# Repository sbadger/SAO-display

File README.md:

# SAO-display
Display board for SAO

My goals for this project
* create an A4 size display board with a 4x5 grid of SAO connectors
* I2c connectors should be connected so the SAO's can talk
* I2c connectoer near incoming power connector to tap into the bus
* I2c bus and clock should be easily connected or disconnected through hsolder brige or header
* expose the GPIO pins to an unpopulated header to enable if needed
* mounting holes in corners
* LED power light
* 3.3V reguator for each row

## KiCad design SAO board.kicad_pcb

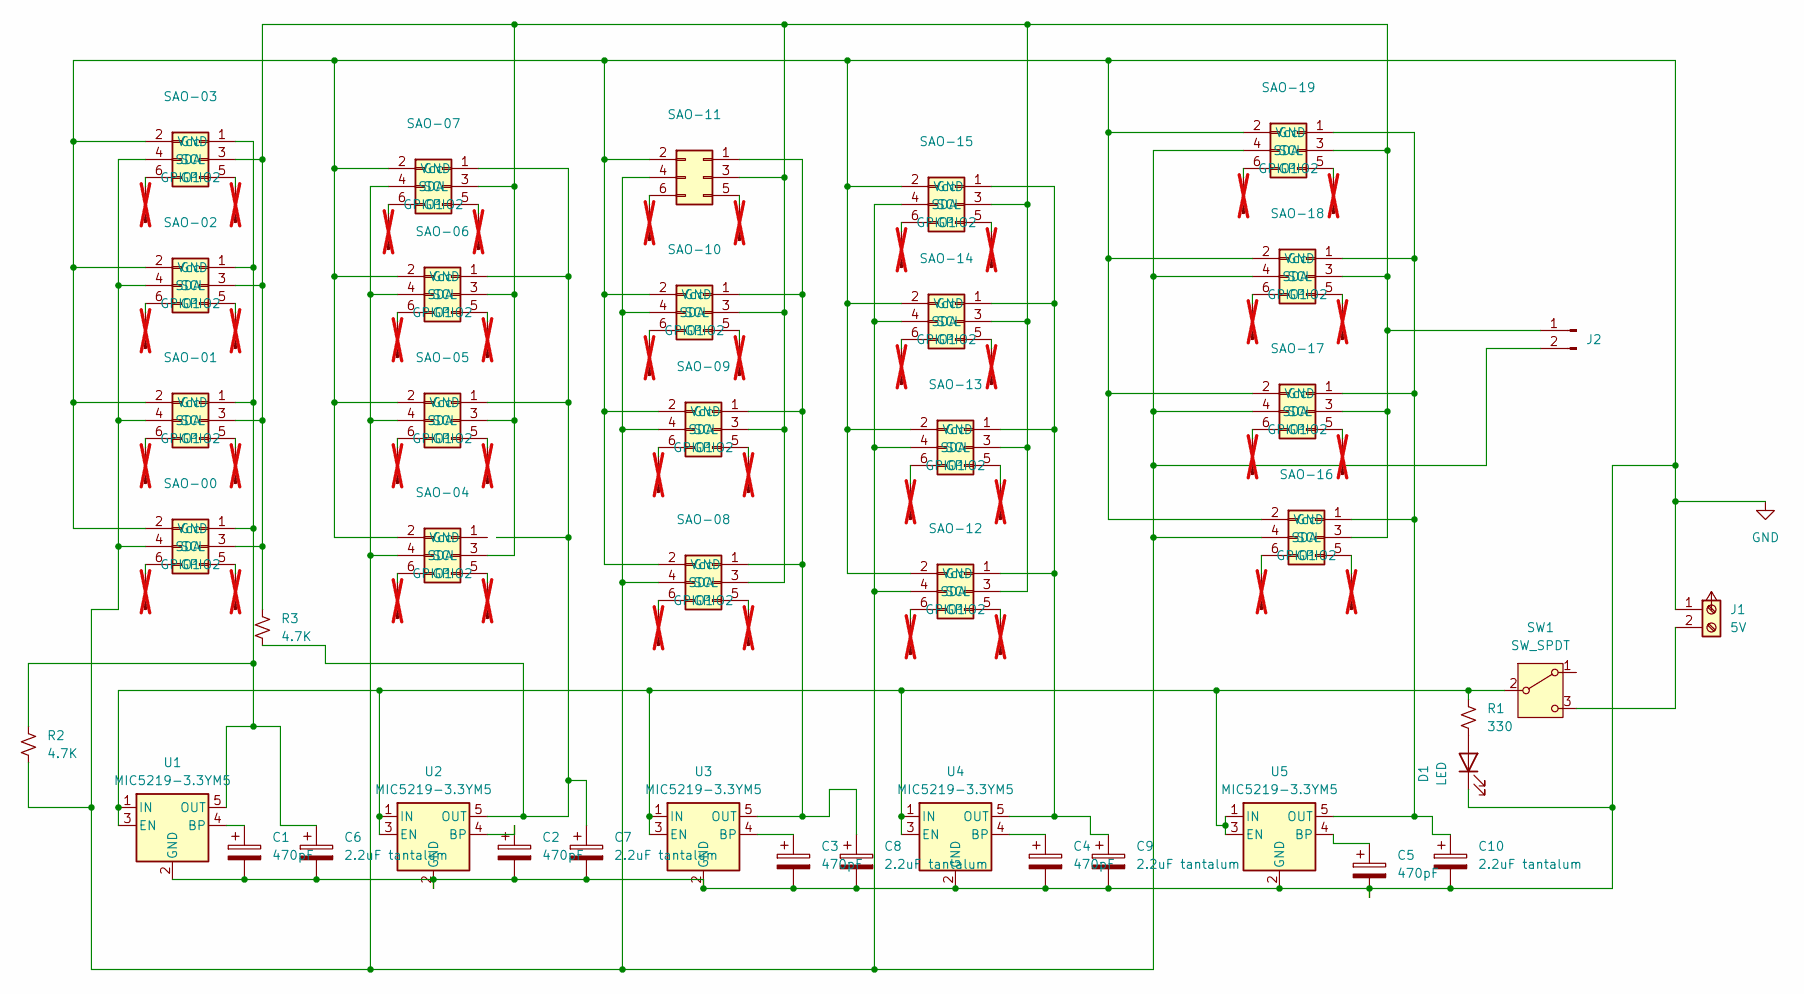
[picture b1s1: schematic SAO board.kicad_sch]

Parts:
C1, C2, C3, C4, C5: 470pF; L_1008_2520Metric
C6, C7, C8, C9, C10: 2.2uF tantalum; L_1008_2520Metric
D1: LED; L_1008_2520Metric
J1: 5V; TerminalBlock_Phoenix_PT-1,5-2-5.0-H_1x02_P5.00mm_Horizontal
J2: PinHeader_1x02_P2.54mm_Vertical
J3, J4, J5, J6, J7, J8, J9, J10, J11, J12, J13, J14, J15, J16, J17, J18, J19, J20, J21, J22, J23, J24, J25, J26, J27, J28, J29, J30, J31, J32, J33, J34, J35, J36, J37, J38, J39, J40, J41, J42: Conn_01x01_Pin; PinHeader_1x01_P2.54mm_Horizontal; not fitted
R1: 330; L_1008_2520Metric
R2, R3: 4.7K; L_1008_2520Metric
SAO-00, SAO-01, SAO-02, SAO-03, SAO-04, SAO-05, SAO-06, SAO-07, SAO-08, SAO-09, SAO-10, SAO-11, SAO-12, SAO-13, SAO-14, SAO-15, SAO-16, SAO-17, SAO-18, SAO-19: SAO; PinHeader_2x03_P2.54mm_Vertical
SW1: SW_SPDT; SW_Slide-03_Wuerth-WS-SLTV_10x2.5x6.4_P2.54mm
U1, U2, U3, U4, U5: MIC5219-3.3YM5; SOT-23-5

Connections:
GND: C1.2, C2.2, C3.2, C4.2, C5.2, C6.2, C7.2, C8.2, C9.2, C10.2, D1.1 (K), J1.1, SAO-00.2 (GND), SAO-01.2 (GND), SAO-02.2 (GND), SAO-03.2 (GND), SAO-04.2 (GND), SAO-05.2 (GND), SAO-06.2 (GND), SAO-07.2 (GND), SAO-08.2 (GND), SAO-09.2 (GND), SAO-10.2 (GND), SAO-11.2 (GND), SAO-12.2 (GND), SAO-13.2 (GND), SAO-14.2 (GND), SAO-15.2 (GND), SAO-16.2 (GND), SAO-17.2 (GND), SAO-18.2 (GND), SAO-19.2 (GND), U1.2 (GND), U2.2 (GND), U3.2 (GND), U4.2 (GND), U5.2 (GND)
unnamed: D1.2 (A), R1.2
unnamed: J1.2, SW1.3 (C)
unnamed: J2.1, R3.1, SAO-00.3 (SDA), SAO-01.3 (SDA), SAO-02.3 (SDA), SAO-03.3 (SDA), SAO-04.3 (SDA), SAO-05.3 (SDA), SAO-06.3 (SDA), SAO-07.3 (SDA), SAO-08.3 (SDA), SAO-09.3 (SDA), SAO-10.3 (SDA), SAO-11.3 (SDA), SAO-12.3 (SDA), SAO-13.3 (SDA), SAO-14.3 (SDA), SAO-15.3 (SDA), SAO-16.3 (SDA), SAO-17.3 (SDA), SAO-18.3 (SDA), SAO-19.3 (SDA)
unnamed: J2.2, R2.2, SAO-00.4 (SCL), SAO-01.4 (SCL), SAO-02.4 (SCL), SAO-03.4 (SCL), SAO-04.4 (SCL), SAO-05.4 (SCL), SAO-06.4 (SCL), SAO-07.4 (SCL), SAO-08.4 (SCL), SAO-09.4 (SCL), SAO-10.4 (SCL), SAO-11.4 (SCL), SAO-12.4 (SCL), SAO-13.4 (SCL), SAO-14.4 (SCL), SAO-15.4 (SCL), SAO-16.4 (SCL), SAO-17.4 (SCL), SAO-18.4 (SCL), SAO-19.4 (SCL)
unnamed: J3.1, SAO-03.5 (GPIO1)
unnamed: J4.1, SAO-03.6 (GPIO2)
unnamed: J5.1, SAO-02.6 (GPIO2)
unnamed: J6.1, SAO-02.5 (GPIO1)
unnamed: J7.1, SAO-01.5 (GPIO1)
unnamed: J8.1, SAO-01.6 (GPIO2)
unnamed: J9.1, SAO-00.6 (GPIO2)
unnamed: J10.1, SAO-00.5 (GPIO1)
unnamed: J11.1, SAO-07.6 (GPIO2)
unnamed: J12.1, SAO-07.5 (GPIO1)
unnamed: J13.1, SAO-06.5 (GPIO1)
unnamed: J14.1, SAO-06.6 (GPIO2)
unnamed: J15.1, SAO-05.6 (GPIO2)
unnamed: J16.1, SAO-05.5 (GPIO1)
unnamed: J17.1, SAO-04.5 (GPIO1)
unnamed: J18.1, SAO-04.6 (GPIO2)
unnamed: J19.1, SAO-08.6 (GPIO2)
unnamed: J20.1, SAO-08.5 (GPIO1)
unnamed: J21.1, SAO-09.5 (GPIO1)
unnamed: J22.1, SAO-09.6 (GPIO2)
unnamed: J23.1, SAO-10.6 (GPIO2)
unnamed: J24.1, SAO-10.5 (GPIO1)
unnamed: J25.1, SAO-11.5 (GPIO1)
unnamed: J26.1, SAO-11.6 (GPIO2)
unnamed: J27.1, SAO-15.6 (GPIO2)
unnamed: J28.1, SAO-15.5 (GPIO1)
unnamed: J29.1, SAO-14.5 (GPIO1)
unnamed: J30.1, SAO-14.6 (GPIO2)
unnamed: J31.1, SAO-13.5 (GPIO1)
unnamed: J32.1, SAO-13.6 (GPIO2)
unnamed: J33.1, SAO-12.6 (GPIO2)
unnamed: J34.1, SAO-12.5 (GPIO1)
unnamed: J35.1, SAO-19.6 (GPIO2)
unnamed: J36.1, SAO-19.5 (GPIO1)
unnamed: J37.1, SAO-18.5 (GPIO1)
unnamed: J38.1, SAO-18.6 (GPIO2)
unnamed: J39.1, SAO-17.6 (GPIO2)
unnamed: J40.1, SAO-17.5 (GPIO1)
unnamed: J41.1, SAO-16.6 (GPIO2)
unnamed: J42.1, SAO-16.5 (GPIO1)
unnamed: C6.1, R2.1, SAO-00.1 (Vcc), SAO-01.1 (Vcc), SAO-02.1 (Vcc), SAO-03.1 (Vcc), U1.5 (OUT)
unnamed: C7.1, R3.2, SAO-05.1 (Vcc), SAO-06.1 (Vcc), SAO-07.1 (Vcc), U2.5 (OUT)
unnamed: C8.1, SAO-08.1 (Vcc), SAO-09.1 (Vcc), SAO-10.1 (Vcc), SAO-11.1 (Vcc), U3.5 (OUT)
unnamed: C9.1, SAO-12.1 (Vcc), SAO-13.1 (Vcc), SAO-14.1 (Vcc), SAO-15.1 (Vcc), U4.5 (OUT)
unnamed: C10.1, SAO-16.1 (Vcc), SAO-17.1 (Vcc), SAO-18.1 (Vcc), SAO-19.1 (Vcc), U5.5 (OUT)
unnamed: R1.1, SW1.2 (B), U1.1 (IN), U1.3 (EN), U2.1 (IN), U2.3 (EN), U3.1 (IN), U3.3 (EN), U4.1 (IN), U4.3 (EN), U5.1 (IN), U5.3 (EN)
unnamed: C1.1, U1.4 (BP)
unnamed: C2.1, U2.4 (BP)
unnamed: C3.1, U3.4 (BP)
unnamed: C4.1, U4.4 (BP)
unnamed: C5.1, U5.4 (BP)

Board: 2 copper layers, 82 parts (0 on the bottom side), 56 nets, no tracks yet.

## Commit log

2024-08-29 Add files via upload
    First crack at the 4x5 SAO board schematic
2024-09-03 inital try
    I think the general layout doesn't look bad, but need to route the wires better and apply the silkscreen
2024-09-24 updated circuit and layout
